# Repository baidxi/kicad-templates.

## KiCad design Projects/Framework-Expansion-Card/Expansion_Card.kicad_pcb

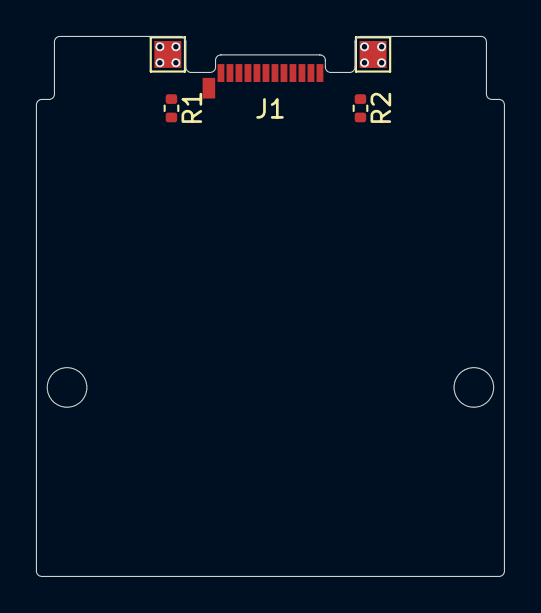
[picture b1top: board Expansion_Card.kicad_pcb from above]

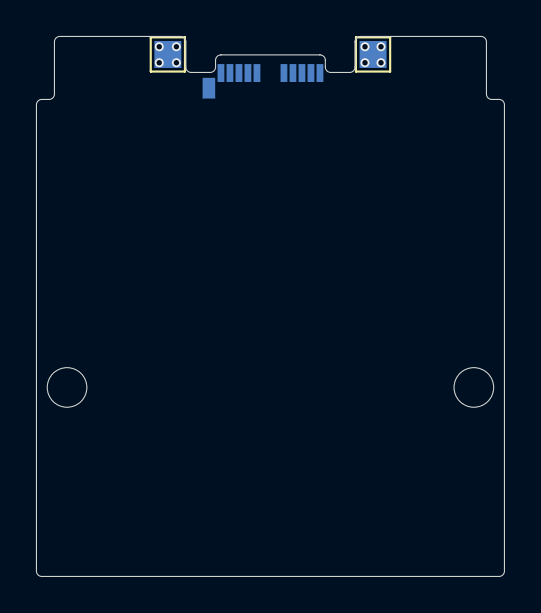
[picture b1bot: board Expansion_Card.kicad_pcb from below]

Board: 2 copper layers, 26.0 x 30.0 mm, 9 parts (2 on the bottom side), 4 nets, no tracks yet.

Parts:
H1, H2: MountingHole; MountingHole_2.2mm_M2
J1: USB_C_Receptacle_USB2.0_14P; USB_C_Plug_Molex_105444
R1, R2: 5k1; R_0402_1005Metric
TP1, TP2, TP3, TP4: TestPoint; TestPoint_Pad_1.5x1.5mm

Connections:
GND: J1.A1 (GND), J1.A12 (GND), J1.B1 (GND), J1.B12 (GND), J1.S1 (SHIELD), R1.1, R2.1, TP1.1, TP2.1, TP3.1, TP4.1
unnamed: J1.A5 (CC1), R1.2
unnamed: J1.B5 (CC2), R2.2
VBUS: J1.A4 (VBUS), J1.A9 (VBUS), J1.B4 (VBUS), J1.B9 (VBUS)

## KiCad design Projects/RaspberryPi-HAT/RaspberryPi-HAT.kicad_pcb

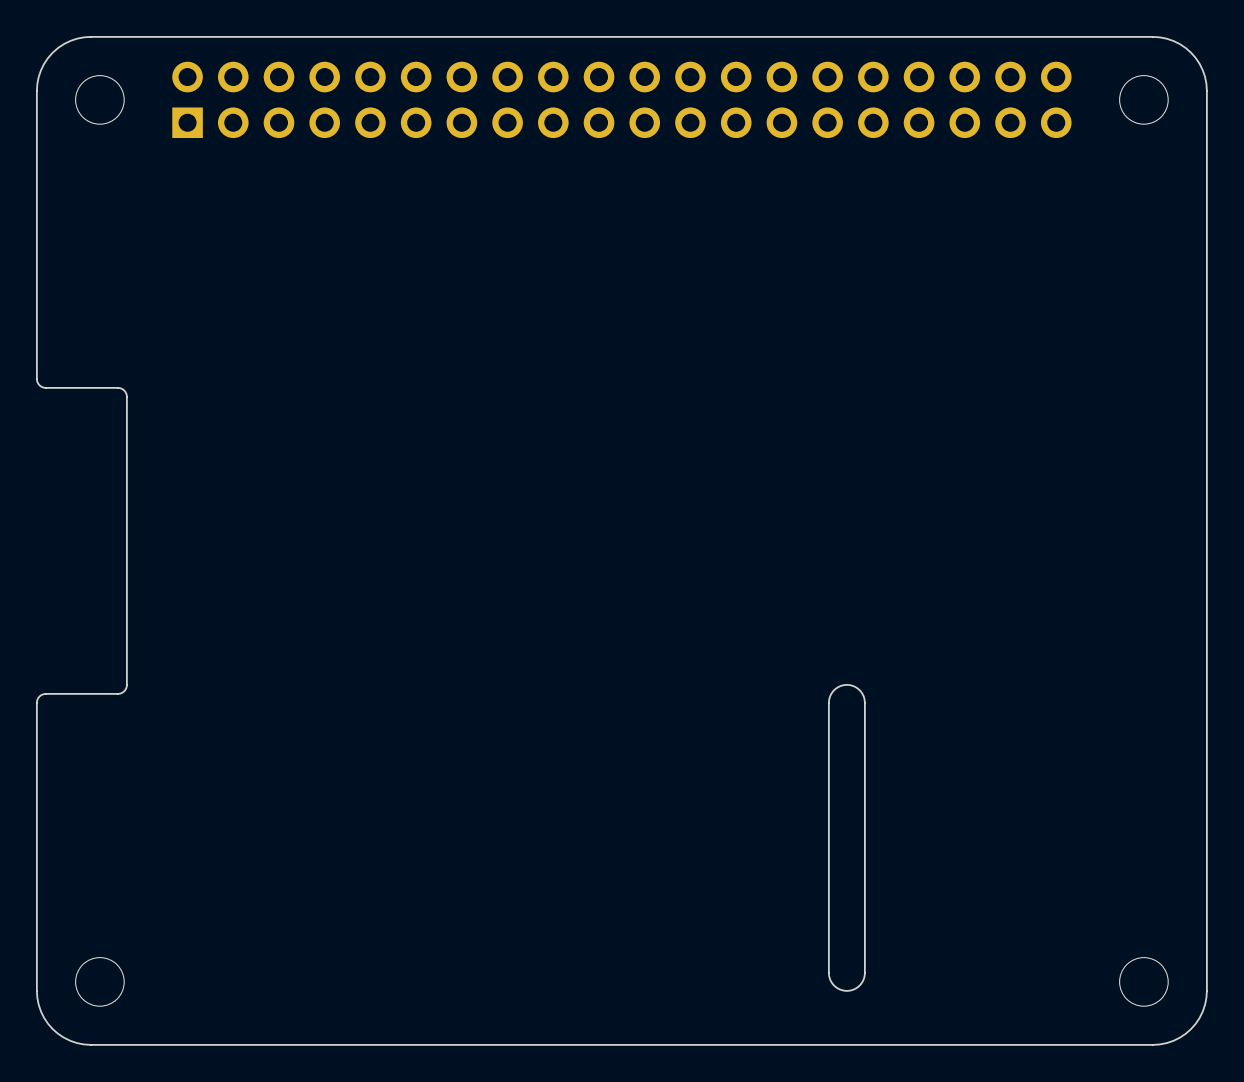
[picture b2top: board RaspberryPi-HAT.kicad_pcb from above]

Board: 2 copper layers, 65.0 x 56.0 mm, 5 parts (1 on the bottom side), 3 nets, no tracks yet.

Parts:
J1: GPIO; PinSocket_2x20_P2.54mm_Vertical
MH1, MH2, MH3, MH4: MountingHole_2.7mm_M2.5

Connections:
+3V3: J1.1, J1.17
+5V: J1.2, J1.4
GND: J1.6, J1.9, J1.14, J1.20, J1.25, J1.30, J1.34, J1.39

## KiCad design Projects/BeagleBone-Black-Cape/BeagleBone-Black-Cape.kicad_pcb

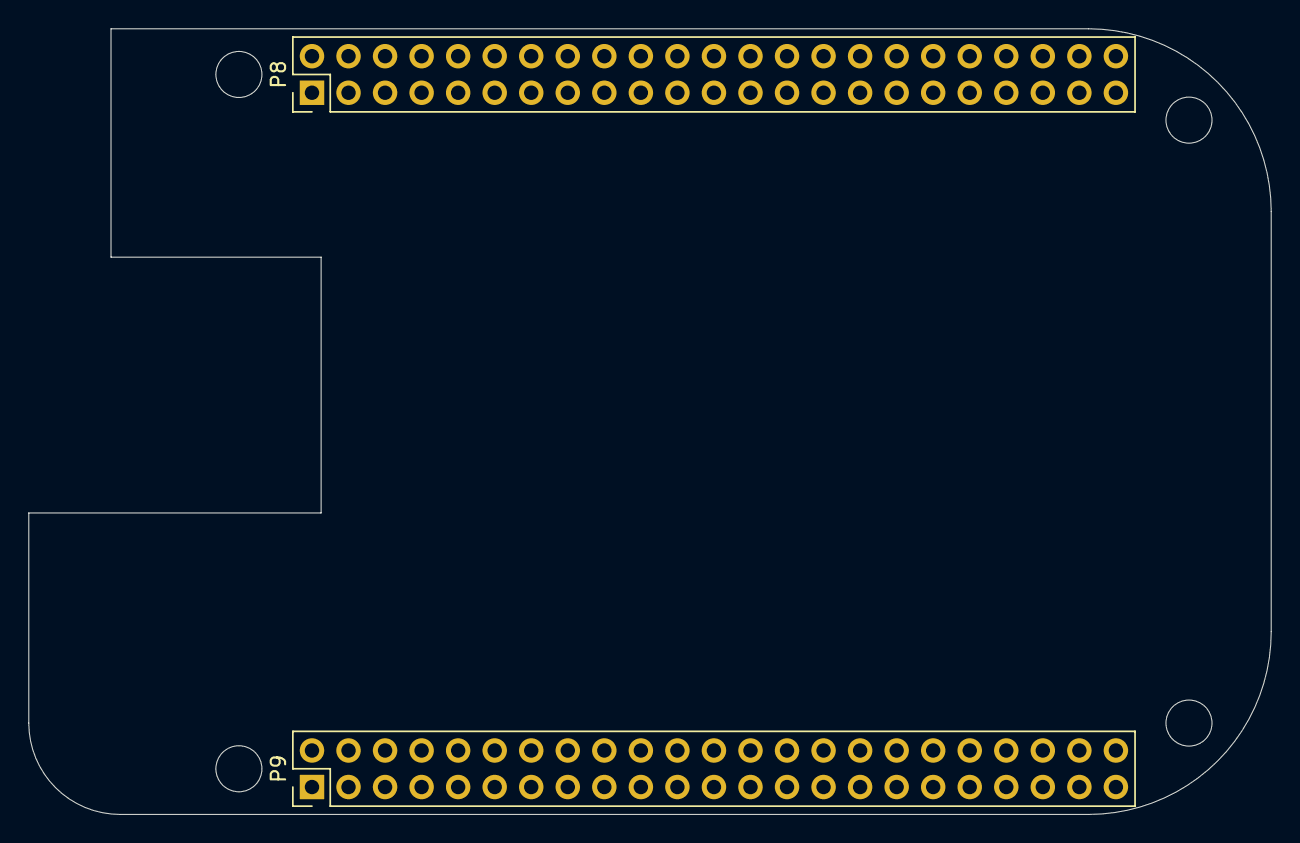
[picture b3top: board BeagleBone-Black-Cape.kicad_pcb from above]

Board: 2 copper layers, 86.4 x 54.6 mm, 6 parts (0 on the bottom side), 4 nets, no tracks yet.

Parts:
MH1, MH2, MH3, MH4: MountingHole_3.2mm_M3_DIN965
P8, P9: BeagleBone_Black_Header; PinHeader_2x23_P2.54mm_Vertical

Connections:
+3V3: P9.3, P9.4
+5V: P9.5, P9.6
GNDD: P8.1, P8.2, P8.45, P9.1, P9.2, P9.43, P9.44, P9.45, P9.46
VBUS: P9.7, P9.8

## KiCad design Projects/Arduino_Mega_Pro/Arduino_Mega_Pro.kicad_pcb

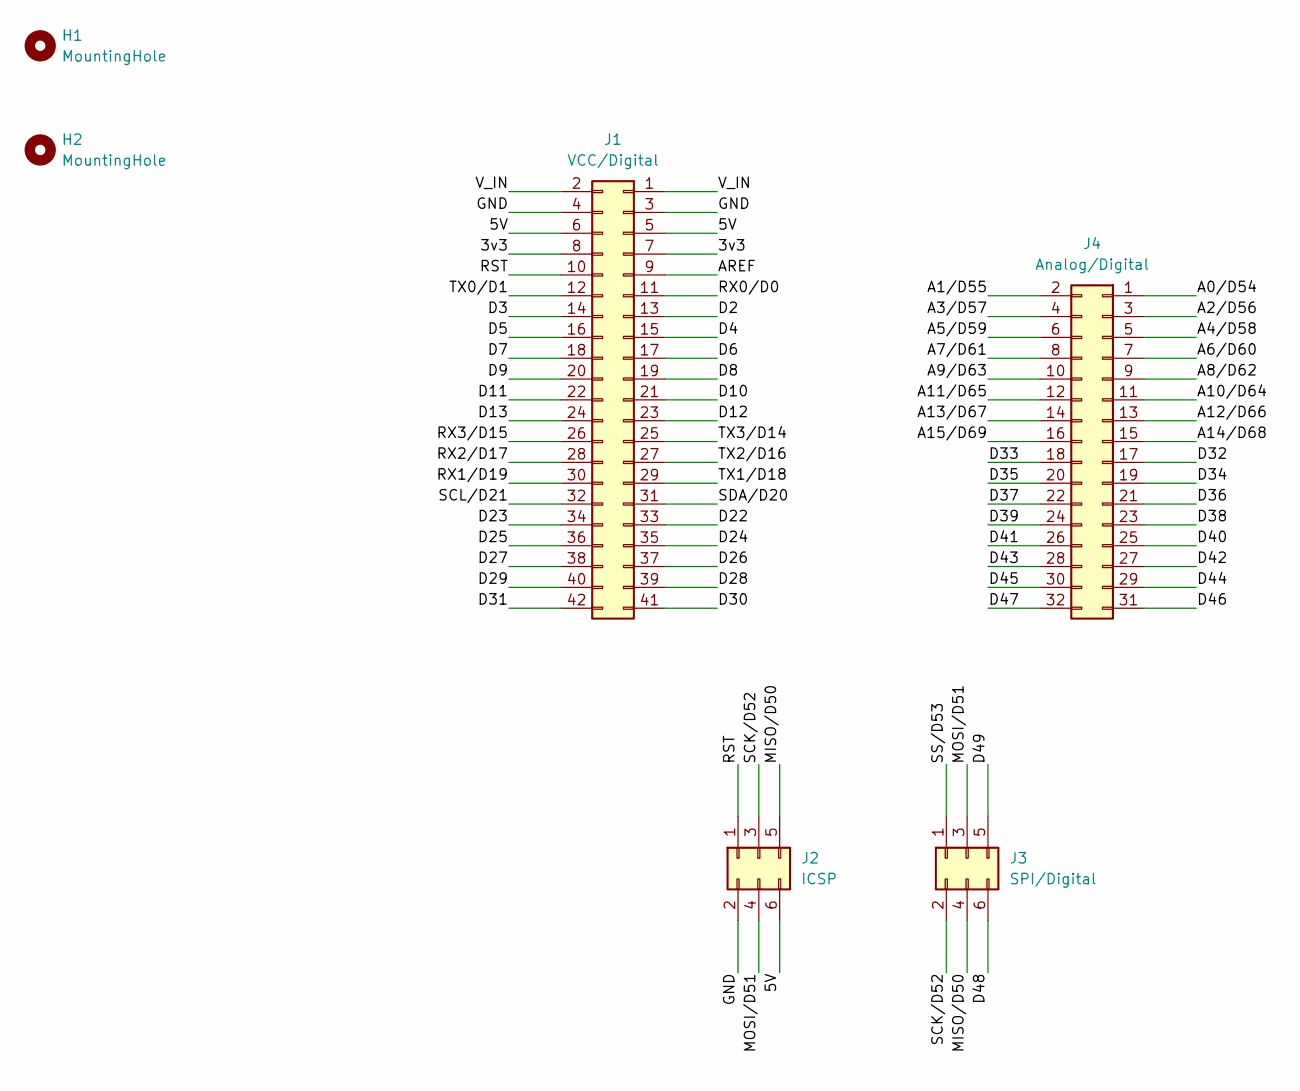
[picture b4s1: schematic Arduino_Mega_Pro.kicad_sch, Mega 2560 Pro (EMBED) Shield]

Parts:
H1, H2: MountingHole; MountingHole_3mm
J1: VCC/Digital; PinSocket_2x21_P2.54mm_Vertical
J2: ICSP; PinSocket_2x03_P2.54mm_Vertical
J3: SPI/Digital; PinSocket_2x03_P2.54mm_Vertical
J4: Analog/Digital; PinSocket_2x16_P2.54mm_Vertical

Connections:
/3v3: J1.7, J1.8
/5V: J1.5, J1.6, J2.6
/A0/D54: J4.1
/A1/D55: J4.2
/A2/D56: J4.3
/A3/D57: J4.4
/A4/D58: J4.5
/A5/D59: J4.6
/A6/D60: J4.7
/A7/D61: J4.8
/A8/D62: J4.9
/A9/D63: J4.10
/A10/D64: J4.11
/A11/D65: J4.12
/A12/D66: J4.13
/A13/D67: J4.14
/A14/D68: J4.15
/A15/D69: J4.16
/AREF: J1.9
/D2: J1.13
/D3: J1.14
/D4: J1.15
/D5: J1.16
/D6: J1.17
/D7: J1.18
/D8: J1.19
/D9: J1.20
/D10: J1.21
/D11: J1.22
/D12: J1.23
/D13: J1.24
/D22: J1.33
/D23: J1.34
/D24: J1.35
/D25: J1.36
/D26: J1.37
/D27: J1.38
/D28: J1.39
/D29: J1.40
/D30: J1.41
/D31: J1.42
/D32: J4.17
/D33: J4.18
/D34: J4.19
/D35: J4.20
/D36: J4.21
/D37: J4.22
/D38: J4.23
/D39: J4.24
/D40: J4.25
/D41: J4.26
/D42: J4.27
/D43: J4.28
/D44: J4.29
/D45: J4.30
/D46: J4.31
/D47: J4.32
/D48: J3.6
/D49: J3.5
/GND: J1.3, J1.4, J2.2
/MISO/D50: J2.5, J3.4
/MOSI/D51: J2.4, J3.3
/RST: J1.10, J2.1
/RX0/D0: J1.11
/RX1/D19: J1.30
/RX2/D17: J1.28
/RX3/D15: J1.26
/SCK/D52: J2.3, J3.2
/SCL/D21: J1.32
/SDA/D20: J1.31
/SS/D53: J3.1
/TX0/D1: J1.12
/TX1/D18: J1.29
/TX2/D16: J1.27
/TX3/D14: J1.25
/V_IN: J1.1, J1.2

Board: 2 copper layers, 6 parts (0 on the bottom side), 8 nets, no tracks yet.

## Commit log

2022-10-06 Mega Pro template added
2023-01-06 Restore accidentally deleted stm32 template
2023-01-06 Fix v6 net names
2024-01-26 worksheets: Add VCS optimized worksheet
    When having worksheets stored in a version control system, the version,
    date etc fields shouldn't be filled manually. Instead, we should get
    these from our VCS.
    This does require the user to use commit hooks, kibot-preflights etc to
    fill these variables.
    VCS_SCH_TIMEDATE: The timestamp to be used for the 'Date' field.
2024-08-19 Add STM32 "Zio" template
2024-08-20 fix extra layers
2025-09-02 Add flipper zero regular and small external module templates
2025-09-14 Add template for Framework Expansion Card
2025-09-14 Add template for Raspberry Pi Camera module 22 FPC
2026-04-29 Update to KiCAD 10
